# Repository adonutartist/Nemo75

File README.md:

# Nemo75
75% Keeb thats ergonomic (hopefully)

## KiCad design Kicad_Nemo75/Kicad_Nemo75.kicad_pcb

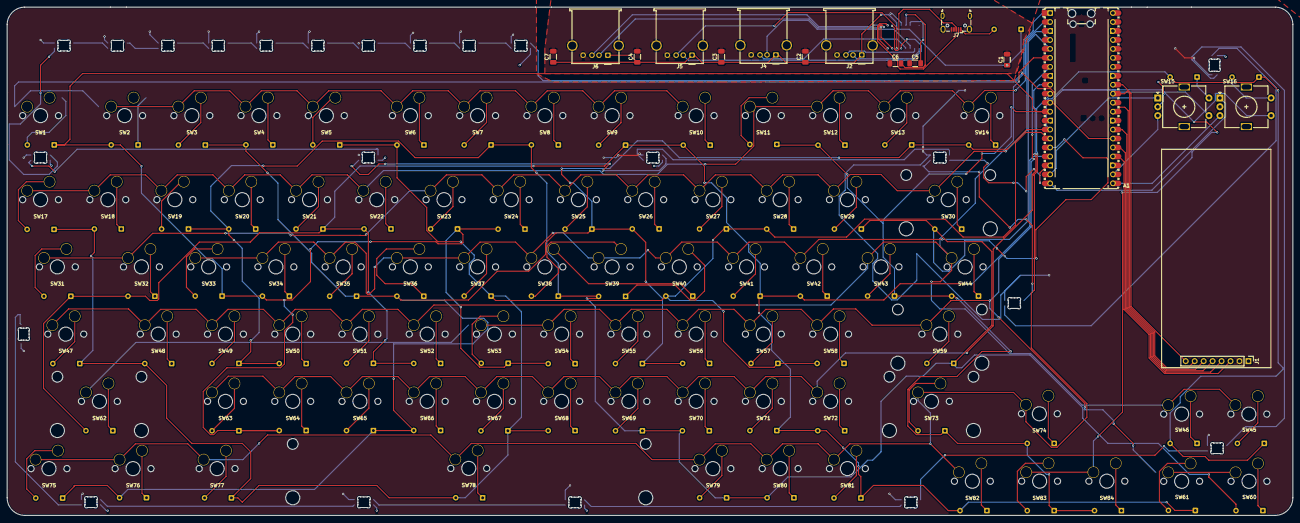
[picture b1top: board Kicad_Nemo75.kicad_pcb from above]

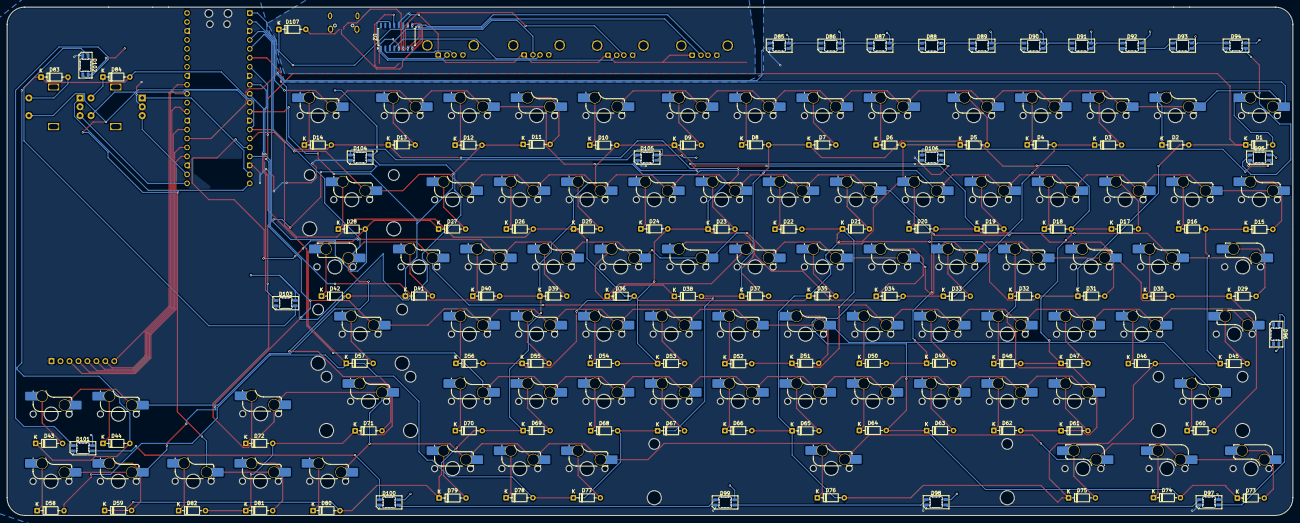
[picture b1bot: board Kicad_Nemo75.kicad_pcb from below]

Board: 2 copper layers, 364.3 x 144.0 mm, 211 parts (108 on the bottom side), 147 nets.

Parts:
A1: RaspberryPi_Pico; RaspberryPi_Pico_Common_Unspecified
C1, C2, C3, C4, C5, C6, C7: C; C_1206_3216Metric_Pad1.33x1.80mm_HandSolder
D1, D2, D3, D4, D5, D6, D7, D8, D9, D10, D11, D12, D13, D14, D15, D16, D17, D18, D19, D20, D21, D22, D23, D24, D25, D26, D27, D28, D29, D30, D31, D32, D33, D34, D35, D36, D37, D38, D39, D40, D41, D42, D43, D44, D45, D46, D47, D48, D49, D50, D51, D52, D53, D54, D55, D56, D57, D58, D59, D60, D61, D62, D63, D64, D65, D66, D67, D68, D69, D70, D71, D72, D73, D74, D75, D76, D77, D78, D79, D80, D81, D82, D83, D84, D107: D; D_DO-35_SOD27_P7.62mm_Horizontal
D85, D86, D87, D88, D89, D90, D91, D92, D93, D94, D95, D96, D97, D98, D99, D100, D101, D102, D103, D104, D105, D106: SK6812; LED_SK6812MINI-E_3.2x2.8mm_P1.5mm_ReverseMount
J1: Conn_01x08_Pin; PinHeader_1x08_P2.54mm_Vertical
J2, J4, J5, J6: USB_A; USB_A_Molex_67643_Horizontal
J7: USB_B_Micro; USB_Micro-B_Wuerth_629105150521
S1: MX_stab; STAB_MX_6.25u
S2, S4: MX_stab; STAB_MX_2u
S3: MX_stab; STAB_MX_2.75u
S5: MX_stab; STAB_MX_2.25u
SW1, SW2, SW3, SW4, SW5, SW6, SW7, SW8, SW9, SW10, SW11, SW12, SW13, SW14, SW17, SW18, SW19, SW20, SW21, SW22, SW23, SW24, SW25, SW26, SW27, SW28, SW29, SW30, SW32, SW33, SW34, SW35, SW36, SW37, SW38, SW39, SW40, SW41, SW42, SW43, SW45, SW46, SW48, SW49, SW50, SW51, SW52, SW53, SW54, SW55, SW56, SW57, SW58, SW59, SW60, SW61, SW62, SW63, SW64, SW65, SW66, SW67, SW68, SW69, SW70, SW71, SW72, SW73, SW74, SW78, SW79, SW80, SW81, SW82, SW83, SW84: SW_Push; SW_MX_HS_CPG151101S11_1u
SW15, SW16: RotaryEncoder_Switch; RotaryEncoder_Alps_EC11E-Switch_Vertical_H20mm
SW31, SW44: SW_Push; SW_MX_HS_CPG151101S11_1.5u
SW47: SW_Push; SW_MX_HS_CPG151101S11_1.75u
SW75, SW76, SW77: SW_Push; SW_MX_HS_CPG151101S11_1.25u
U2: SL2.1A; SOIC-16_4.55x10.3mm_P1.27mm

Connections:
+3.3V: A1.36 (3V3), D85.3 (VDD), D86.3 (VDD), D87.3 (VDD), D88.3 (VDD), D89.3 (VDD), D90.3 (VDD), D91.3 (VDD), D92.3 (VDD), D93.3 (VDD), D94.3 (VDD), D95.3 (VDD), D96.3 (VDD), D97.3 (VDD), D98.3 (VDD), D99.3 (VDD), D100.3 (VDD), D101.3 (VDD), D102.3 (VDD), D103.3 (VDD), D104.3 (VDD), D105.3 (VDD), D106.3 (VDD), J1.2 (VCC)
+5V: C1.1, C2.1, C3.1, C4.1, C7.1, D107.1 (K), J2.1 (VBUS), J4.1 (VBUS), J5.1 (VBUS), J6.1 (VBUS), U2.11 (VCC5V)
BLK: A1.32 (GPIO27_ADC1), J1.8 (BLK)
COL 1: A1.12 (GPIO9), D1.1 (K), D2.2 (A), D11.1 (K), D12.2 (A), D21.1 (K), D22.2 (A), D31.1 (K), D32.2 (A), D41.1 (K), D42.2 (A), D51.1 (K), D52.2 (A), D61.1 (K), D62.2 (A), D71.1 (K), D72.2 (A), D81.1 (K), D82.2 (A)
COL 2: A1.14 (GPIO10), D3.1 (K), D4.2 (A), D13.1 (K), D14.2 (A), D23.1 (K), D24.2 (A), D33.1 (K), D34.2 (A), D43.1 (K), D44.2 (A), D53.1 (K), D54.2 (A), D63.1 (K), D64.2 (A), D73.1 (K), D74.2 (A), D83.1 (K), D84.2 (A)
COL 3: A1.15 (GPIO11), D5.1 (K), D6.2 (A), D15.1 (K), D16.2 (A), D25.1 (K), D26.2 (A), D35.1 (K), D36.2 (A), D45.1 (K), D46.2 (A), D55.1 (K), D56.2 (A), D65.1 (K), D66.2 (A), D75.1 (K), D76.2 (A)
COL 4: A1.16 (GPIO12), D7.1 (K), D8.2 (A), D17.1 (K), D18.2 (A), D27.1 (K), D28.2 (A), D37.1 (K), D38.2 (A), D47.1 (K), D48.2 (A), D57.1 (K), D58.2 (A), D67.1 (K), D68.2 (A), D77.1 (K), D78.2 (A)
COL 5: A1.17 (GPIO13), D9.1 (K), D10.2 (A), D19.1 (K), D20.2 (A), D29.1 (K), D30.2 (A), D39.1 (K), D40.2 (A), D49.1 (K), D50.2 (A), D59.1 (K), D60.2 (A), D69.1 (K), D70.2 (A), D79.1 (K), D80.2 (A)
CS: A1.31 (GPIO26_ADC0), J1.7 (CS)
DC: A1.29 (GPIO22), J1.6 (DC)
GND: A1.3 (GND), A1.8 (GND), A1.13 (GND), A1.18 (GND), A1.23 (GND), A1.28 (GND), A1.38 (GND), D85.1 (VSS), D86.1 (VSS), D87.1 (VSS), D88.1 (VSS), D89.1 (VSS), D90.1 (VSS), D91.1 (VSS), D92.1 (VSS), D93.1 (VSS), D94.1 (VSS), D95.1 (VSS), D96.1 (VSS), D97.1 (VSS), D98.1 (VSS), D99.1 (VSS), D100.1 (VSS), D101.1 (VSS), D102.1 (VSS), D103.1 (VSS), D104.1 (VSS), D105.1 (VSS), D106.1 (VSS), J1.1 (GND), SW15.C, SW16.C
GND1: C1.2, C2.2, C3.2, C4.2, C5.1, C6.1, C7.2, J2.4 (GND), J2.SH (Shield), J4.4 (GND), J4.SH (Shield), J5.4 (GND), J5.SH (Shield), J6.4 (GND), J6.SH (Shield), J7.5 (GND), J7.SH (Shield), U2.12 (GND), U2.16 (XIN)
IN+: J7.3 (D+), U2.10 (UDP)
IN-: J7.2 (D-), U2.9 (UDM)
LED: A1.26 (GPIO20), D85.2 (DIN)
unnamed: D1.2 (A), SW1.2
unnamed: D2.1 (K), SW2.2
unnamed: D3.2 (A), SW3.2
unnamed: D4.1 (K), SW4.2
unnamed: D5.2 (A), SW5.2
unnamed: D6.1 (K), SW6.2
unnamed: D7.2 (A), SW7.2
unnamed: D8.1 (K), SW8.2
unnamed: D9.2 (A), SW9.2
unnamed: D10.1 (K), SW10.2
unnamed: D11.2 (A), SW11.2
unnamed: D12.1 (K), SW12.2
unnamed: D13.2 (A), SW13.2
unnamed: D14.1 (K), SW14.2
unnamed: D15.2 (A), SW17.2
unnamed: D16.1 (K), SW18.2
unnamed: D17.2 (A), SW19.2
unnamed: D18.1 (K), SW20.2
unnamed: D19.2 (A), SW21.2
unnamed: D20.1 (K), SW22.2
unnamed: D21.2 (A), SW23.2
unnamed: D22.1 (K), SW24.2
unnamed: D23.2 (A), SW25.2
unnamed: D24.1 (K), SW26.2
unnamed: D25.2 (A), SW27.2
unnamed: D26.1 (K), SW28.2
unnamed: D27.2 (A), SW29.2
unnamed: D28.1 (K), SW30.2
unnamed: D29.2 (A), SW31.2
unnamed: D30.1 (K), SW32.2
unnamed: D31.2 (A), SW33.2
unnamed: D32.1 (K), SW34.2
unnamed: D33.2 (A), SW35.2
unnamed: D34.1 (K), SW36.2
unnamed: D35.2 (A), SW37.2
unnamed: D36.1 (K), SW38.2
unnamed: D37.2 (A), SW39.2
unnamed: D38.1 (K), SW40.2
unnamed: D39.2 (A), SW41.2
unnamed: D40.1 (K), SW42.2
unnamed: D41.2 (A), SW43.2
unnamed: D42.1 (K), SW44.2
unnamed: D43.2 (A), SW45.2
unnamed: D44.1 (K), SW46.2
unnamed: D45.2 (A), SW47.2
unnamed: D46.1 (K), SW48.2
unnamed: D47.2 (A), SW49.2
unnamed: D48.1 (K), SW50.2
unnamed: D49.2 (A), SW51.2
unnamed: D50.1 (K), SW52.2
unnamed: D51.2 (A), SW53.2
unnamed: D52.1 (K), SW54.2
unnamed: D53.2 (A), SW55.2
unnamed: D54.1 (K), SW56.2
unnamed: D55.2 (A), SW57.2
unnamed: D56.1 (K), SW58.2
unnamed: D57.2 (A), SW59.2
unnamed: D58.1 (K), SW60.2
unnamed: D59.2 (A), SW61.2
unnamed: D60.1 (K), SW62.2
unnamed: D61.2 (A), SW63.2
unnamed: D62.1 (K), SW64.2
unnamed: D63.2 (A), SW65.2
unnamed: D64.1 (K), SW66.2
unnamed: D65.2 (A), SW67.2
unnamed: D66.1 (K), SW68.2
unnamed: D67.2 (A), SW69.2
unnamed: D68.1 (K), SW70.2
unnamed: D69.2 (A), SW71.2
unnamed: D70.1 (K), SW72.2
unnamed: D71.2 (A), SW73.2
unnamed: D72.1 (K), SW74.2
unnamed: D73.2 (A), SW75.2
unnamed: D74.1 (K), SW76.2
unnamed: D75.2 (A), SW77.2
unnamed: D76.1 (K), SW78.2
unnamed: D77.2 (A), SW79.2
unnamed: D78.1 (K), SW80.2
unnamed: D79.2 (A), SW81.2
unnamed: D80.1 (K), SW82.2
unnamed: D81.2 (A), SW83.2
unnamed: D82.1 (K), SW84.2
unnamed: D85.4 (DOUT), D86.2 (DIN)
unnamed: D86.4 (DOUT), D87.2 (DIN)
unnamed: D87.4 (DOUT), D88.2 (DIN)
unnamed: D88.4 (DOUT), D89.2 (DIN)
unnamed: D89.4 (DOUT), D90.2 (DIN)
unnamed: D90.4 (DOUT), D91.2 (DIN)
unnamed: D91.4 (DOUT), D92.2 (DIN)
unnamed: D92.4 (DOUT), D93.2 (DIN)
unnamed: D93.4 (DOUT), D94.2 (DIN)
unnamed: D94.4 (DOUT), D95.2 (DIN)
unnamed: D96.2 (DIN), D97.4 (DOUT)
unnamed: D97.2 (DIN), D98.4 (DOUT)
unnamed: D98.2 (DIN), D99.4 (DOUT)
unnamed: D100.2 (DIN), D101.4 (DOUT)
unnamed: D99.2 (DIN), D100.4 (DOUT)
unnamed: D101.2 (DIN), D102.4 (DOUT)
unnamed: D102.2 (DIN), D103.4 (DOUT)
unnamed: D103.2 (DIN), D104.4 (DOUT)
unnamed: D104.2 (DIN), D105.4 (DOUT)
unnamed: D105.2 (DIN), D106.4 (DOUT)
unnamed: D95.4 (DOUT), D106.2 (DIN)
unnamed: D107.2 (A), J7.1 (VBUS)
unnamed: J2.3 (D+), U2.2 (DP4)
unnamed: J2.2 (D-), U2.1 (DM4)
unnamed: J4.3 (D+), U2.4 (DP3)
unnamed: J4.2 (D-), U2.3 (DM3)
unnamed: J5.3 (D+), U2.6 (DP2)
unnamed: J5.2 (D-), U2.5 (DM2)
unnamed: J6.3 (D+), U2.8 (DP1)
unnamed: J6.2 (D-), U2.7 (DM1)
unnamed: C6.2, U2.13 (VDD3)
unnamed: C5.2, U2.14 (VDD18)
RE 1: A1.11 (GPIO8), SW15.S1, SW16.S1, SW83.1, SW84.1
RE 1 A: A1.19 (GPIO14), SW15.A
RE 1 B: A1.22 (GPIO17), SW15.B
RE 1 OUT: D83.2 (A), SW16.S2
RE 2 A: A1.20 (GPIO15), SW16.A
RE 2 B: A1.21 (GPIO16), SW16.B
RE 2 OUT: D84.1 (K), SW15.S2
RES: A1.27 (GPIO21), J1.5 (RES)
ROW 1: A1.1 (GPIO0), SW1.1, SW2.1, SW3.1, SW4.1, SW5.1, SW6.1, SW7.1, SW8.1, SW9.1, SW10.1
ROW 2: A1.2 (GPIO1), SW11.1, SW12.1, SW13.1, SW14.1, SW17.1, SW18.1, SW19.1, SW20.1, SW21.1, SW22.1
ROW 3: A1.4 (GPIO2), SW23.1, SW24.1, SW25.1, SW26.1, SW27.1, SW28.1, SW29.1, SW30.1, SW31.1, SW32.1
ROW 4: A1.5 (GPIO3), SW33.1, SW34.1, SW35.1, SW36.1, SW37.1, SW38.1, SW39.1, SW40.1, SW41.1, SW42.1
ROW 5: A1.6 (GPIO4), SW43.1, SW44.1, SW45.1, SW46.1, SW47.1, SW48.1, SW49.1, SW50.1, SW51.1, SW52.1
ROW 6: A1.7 (GPIO5), SW53.1, SW54.1, SW55.1, SW56.1, SW57.1, SW58.1, SW59.1, SW60.1, SW61.1, SW62.1
ROW 7: A1.9 (GPIO6), SW63.1, SW64.1, SW65.1, SW66.1, SW67.1, SW68.1, SW69.1, SW70.1, SW71.1, SW72.1
ROW 8: A1.10 (GPIO7), SW73.1, SW74.1, SW75.1, SW76.1, SW77.1, SW78.1, SW79.1, SW80.1, SW81.1, SW82.1
SCL: A1.24 (GPIO18), J1.3 (SCL)
SDA: A1.25 (GPIO19), J1.4 (SDA)
